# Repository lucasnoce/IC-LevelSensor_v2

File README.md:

# IC-LevelSensor_v2
This is version 2 of an IoT device designed to measure water levels using an ultrasonic sensing module and transmit the acquired data via NBIoT.

## Summary
Similar to version 1, the system employs an AJ-SR04M ultrasonic sensing module now connected to a STM32L476RGT6 microcontroller. This module measures the time interval it takes for an ultrasonic wave to travel from the transducer to the water level and back. By calculating the distance based on the time duration, the speed of sound, and dividing the result by 2, the accurate water level is determined. As the speed of sound varies based on factors such as temperature, humidity, and pressure, a SHT31-DIS sensor is incorporated to measure temperature and humidity (pressure is assumed constant). This additional information allows for precise estimation of the speed of sound just before each distance measurement is taken.

To transmit data to the TagoIO platform, a SIM7020 NBIoT module is utilized, employing the MQTT protocol. This facilitates the configuration of a comprehensive dashboard displaying variations in water and battery levels, local temperature and humidity over time, making it an excellent solution for monitoring purposes.

The device is specifically designed for deployment in remote environments and operates on battery power. Due to this constraint, the system primarily operates in low-power mode and wakes up periodically. In this initial version of the device, the wake-up period is intentionally kept small, and collected data is transmitted during each wake-up event via NBIoT. This design choice aims to facilitate easier debugging and testing of the device's functionality. Because it is designed to be battery powered, the device can monitor battery voltage through the microcontroller's ADC.

## Designed PCB
The following image shows the designed PCB layout. It incorporates the SMT32, SHT31, SIM7020E and its adjacent circuitry onto the layout, only leaving the AJ-SR04M as an external module. The PCB features a P-Channel MOSFET at power input for low power reverse polarity protection, a selectable current sensing shunt resistor and ESD protection on the USB connector, SIM Card socket and SIM7020 power input tantalum capacitors. Also features IPEX connector for external antenna with impedance matched trace. The board works on 3.3V and can be powered either by 1.5V batteries such as AAA (through TPS613221ADBV DC-DC boost converter) or by the Micro USB type B (through AMS1117-3.3 regulator).

## Software
Still under development, all drivers and functionalities will be implemented from scratch through STM32CubeIDE.

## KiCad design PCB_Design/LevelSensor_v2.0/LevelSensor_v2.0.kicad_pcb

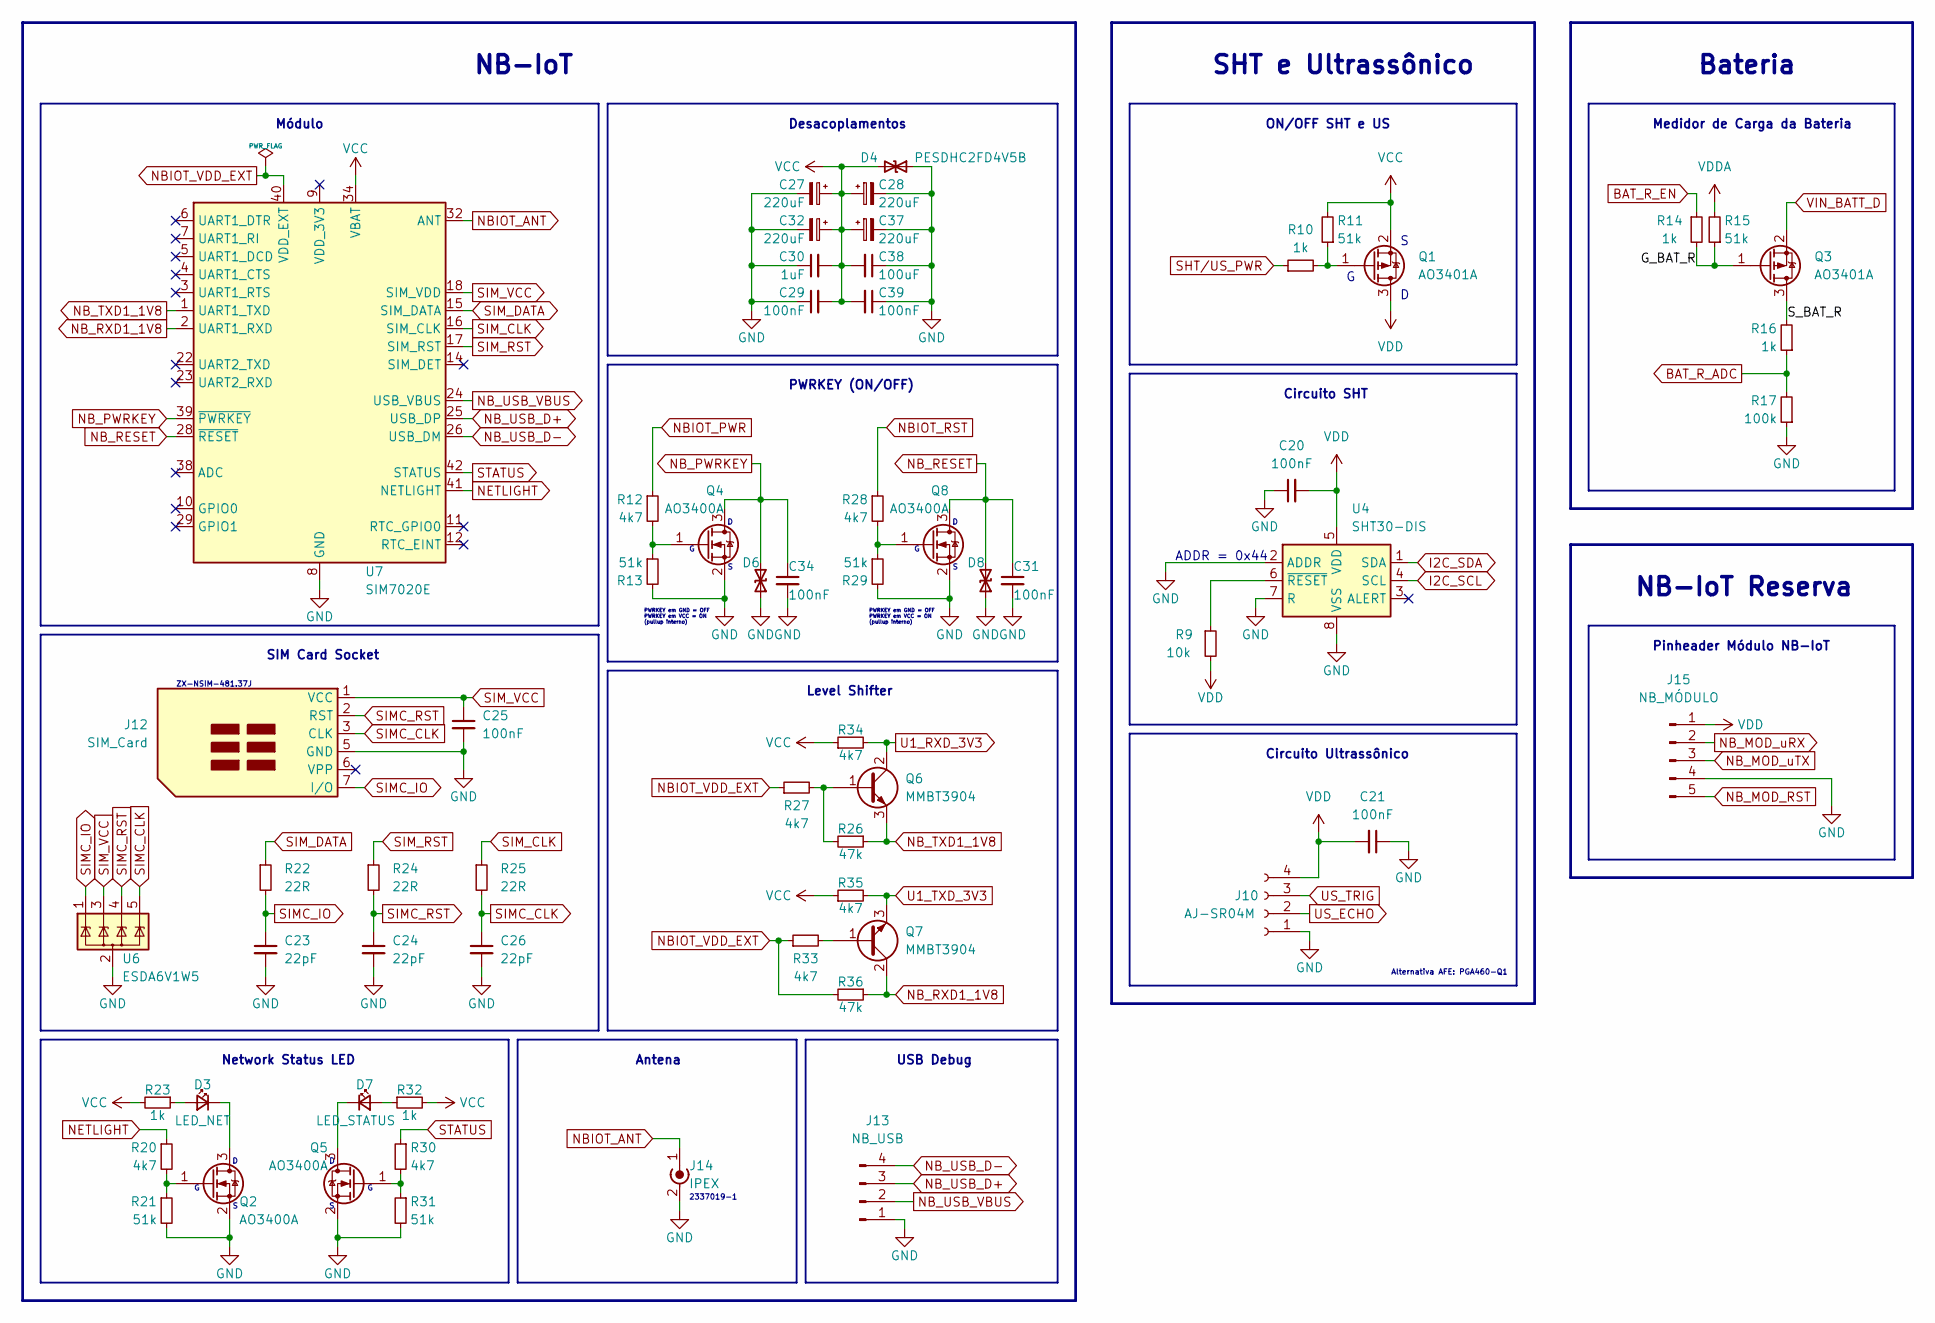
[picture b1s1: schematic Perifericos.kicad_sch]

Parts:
C20, C21: 100nF; C_0603_1608Metric; LCSC Part Number C14663
C23, C24, C26: 22pF; C_0402_1005Metric; LCSC Part Number C1555
C25, C29, C31, C34, C39: 100nF; C_0402_1005Metric; LCSC Part Number C1525
C27, C28, C32, C37: 220uF; CP_EIA-3528-12_Kemet-T
C30: 1uF; C_0402_1005Metric; LCSC Part Number C52923
C38: 100uF; C_1206_3216Metric; LCSC Part Number C15008
D3: LED_NET; LED_0603_1608Metric; LCSC Part Number C2286
D4, D6, D8: PESDHC2FD4V5B; D_TVS_DFN1006-2L
D7: LED_STATUS; LED_0603_1608Metric; LCSC Part Number C72041
J10: AJ-SR04M
J12: SIM_Card; NanoSIMCard-Socket_ZX-NSIM-281.4J
J13: NB_USB; PinHeader_1x04_P2.54mm_Vertical
J14: IPEX; Conn_RF_Receptacle_SMT-TE_2337019-1
J15: NB_MÓDULO; PinHeader_1x05_P2.54mm_Vertical
Q1, Q3: AO3401A; SOT-23; LCSC Part Number C15127
Q2, Q4, Q5, Q8: AO3400A; SOT-23; LCSC Part Number C20917
Q6, Q7: MMBT3904; TBJ_SOT-23; LCSC Part Number C20526
R9: 10k; R_0603_1608Metric; LCSC Part Number C25804
R10, R14, R16, R23, R32: 1k; R_0603_1608Metric; LCSC Part Number C21190
R11, R13, R15, R21, R29, R31: 51k; R_0603_1608Metric; LCSC Part Number C23196
R12, R20, R27, R28, R30, R33, R34, R35: 4k7; R_0603_1608Metric; LCSC Part Number C23162
R17: 100k; R_0603_1608Metric; LCSC Part Number C25803
R22, R24, R25: 22R; R_0402_1005Metric; LCSC Part Number C25092
R26, R36: 47k; R_0603_1608Metric; LCSC Part Number C25819
U4: SHT30-DIS; Sensirion_DFN-8-1EP_2.5x2.5mm_P0.5mm_EP1.1x1.7mm; LCSC Part Number C2687423
U6: ESDA6V1W5; SOT323-5L; LCSC Part Number C167129
U7: SIM7020E; SIMCom_SIM800C; LCSC Part Number C194746

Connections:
/Perifericos/G_BAT_R: Q3.1 (G), R14.2, R15.1
/Perifericos/S_BAT_R: Q3.3 (D), R16.2
BAT_R_ADC: R16.1, R17.2; also elsewhere on the board
BAT_R_EN: R14.1; also elsewhere on the board
GND: C20.1, C21.1, C23.2, C24.2, C25.2, C26.2, C27.2, C28.2, C29.1, C30.1, C31.2, C32.2, C34.2, C37.2, C38.1, C39.1, D4.1 (A1), D6.1 (A1), D8.1 (A1), J10.1, J12.5 (GND), J13.1, J14.2 (Ext), J15.4, Q2.2 (S), Q4.2 (S), Q5.2 (S), Q8.2 (S), R13.2, R17.1, R21.2, R29.2, R31.2, U4.2 (ADDR), U4.7 (R), U4.8 (VSS), U4.9 (VSS), U6.2 (GND), U7.8 (GND), U7.13 (GND), U7.19 (GND), U7.21 (GND), U7.27 (GND), U7.30 (GND), U7.31 (GND), U7.33 (GND), U7.36 (GND), U7.37 (GND); also elsewhere on the board
I2C_SCL: U4.4 (SCL); also elsewhere on the board
I2C_SDA: U4.1 (SDA); also elsewhere on the board
NBIOT_ANT: J14.1 (In), U7.32 (ANT)
NBIOT_PWR: R12.1; also elsewhere on the board
NBIOT_RST: R28.1; also elsewhere on the board
NBIOT_VDD_EXT: R27.1, R33.1, R36.2, U7.40 (VDD_EXT)
NB_MOD_RST: J15.5; also elsewhere on the board
NB_MOD_uRX: J15.2; also elsewhere on the board
NB_MOD_uTX: J15.3; also elsewhere on the board
NB_PWRKEY: C34.1, D6.2 (A2), Q4.3 (D), U7.39 (~PWRKEY)
NB_RESET: C31.1, D8.2 (A2), Q8.3 (D), U7.28 (~RESET)
NB_RXD1_1V8: Q7.2 (C), R36.1, U7.2 (UART1_RXD)
NB_TXD1_1V8: Q6.3 (E), R26.1, U7.1 (UART1_TXD)
NB_USB_D+: J13.3, U7.25 (USB_DP)
NB_USB_D-: J13.4, U7.26 (USB_DM)
NB_USB_VBUS: J13.2, U7.24 (USB_VBUS)
NETLIGHT: R20.1, U7.41 (NETLIGHT)
unnamed: D3.1 (K), Q2.3 (D)
unnamed: D3.2 (A), R23.1
unnamed: D7.1 (K), Q5.3 (D)
unnamed: D7.2 (A), R32.1
unnamed: Q1.1 (G), R10.2, R11.1
unnamed: Q2.1 (G), R20.2, R21.1
unnamed: Q4.1 (G), R12.2, R13.1
unnamed: Q5.1 (G), R30.2, R31.1
unnamed: Q6.1 (B), R26.2, R27.2
unnamed: Q7.1 (B), R33.2
unnamed: Q8.1 (G), R28.2, R29.1
unnamed: R9.1, U4.6 (~RESET)
SHT/US_PWR: R10.1; also elsewhere on the board
SIMC_CLK: C26.1, J12.3 (CLK), R25.2, U6.5 (IO5)
SIMC_IO: C23.1, J12.7 (I/O), R22.2, U6.1 (IO1)
SIMC_RST: C24.1, J12.2 (RST), R24.2, U6.4 (IO4)
SIM_CLK: R25.1, U7.16 (SIM_CLK)
SIM_DATA: R22.1, U7.15 (SIM_DATA)
SIM_RST: R24.1, U7.17 (SIM_RST)
SIM_VCC: C25.1, J12.1 (VCC), U6.3 (IO2), U7.18 (SIM_VDD)
STATUS: R30.1, U7.42 (STATUS)
U1_RXD_3V3: Q6.2 (C), R34.2; also elsewhere on the board
U1_TXD_3V3: Q7.3 (E), R35.2; also elsewhere on the board
US_ECHO: J10.2; also elsewhere on the board
US_TRIG: J10.3; also elsewhere on the board
VCC: C27.1, C28.1, C29.2, C30.2, C32.1, C37.1, C38.2, C39.2, D4.2 (A2), Q1.2 (S), R11.2, R23.2, R32.2, R34.1, R35.1, U7.34 (VBAT), U7.35 (VBAT); also elsewhere on the board
VDD: C20.2, C21.2, J10.4, J15.1, Q1.3 (D), R9.2, U4.5 (VDD)
VDDA: R15.2; also elsewhere on the board
VIN_BATT_D: Q3.2 (S); also elsewhere on the board

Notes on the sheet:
Circuito Ultrassônico
PWRKEY (ON/OFF)
Circuito SHT
PWRKEY em GND = OFF PWRKEY em VCC = ON (pullup interno)
Pinheader Módulo NB-IoT
ON/OFF SHT e US
2337019-1
Network Status LED
USB Debug
NB-IoT Reserva
Antena
NB-IoT
Bateria
Level Shifter
SIM Card Socket
Medidor de Carga da Bateria
SHT e Ultrassônico
Desacoplamentos
ZX-NSIM-481.37J
Alternativa AFE: PGA460-Q1
ADDR = 0x44
Módulo

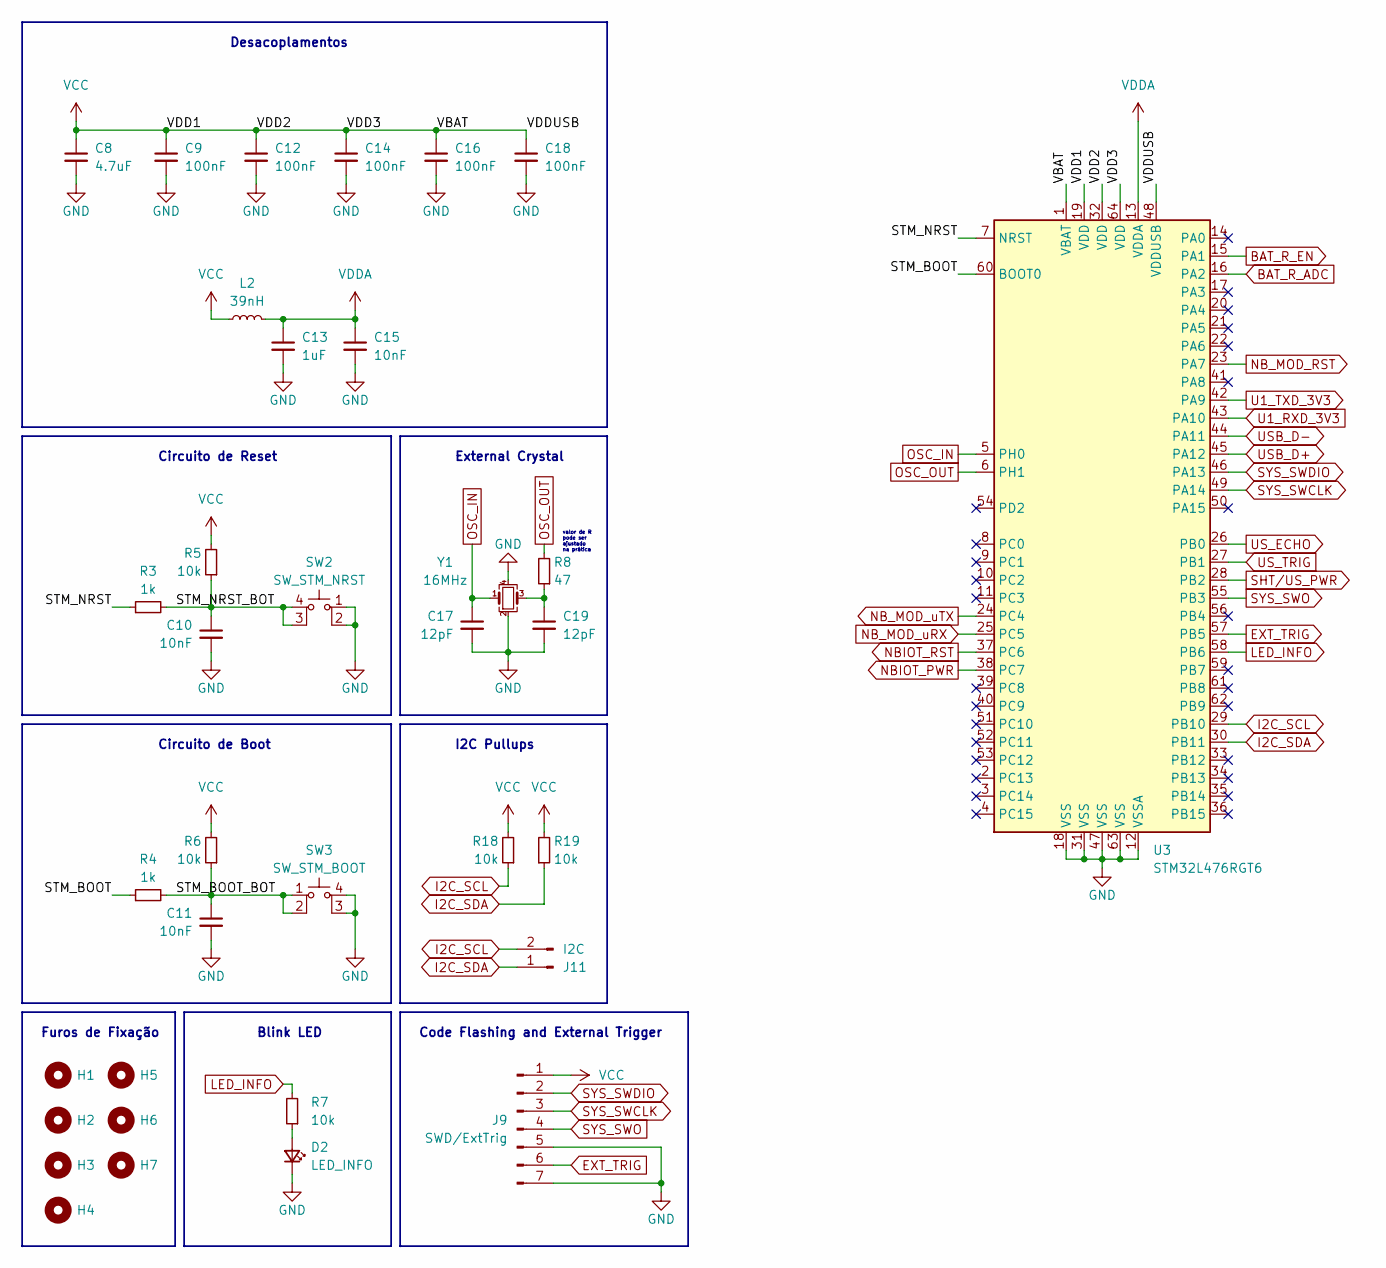
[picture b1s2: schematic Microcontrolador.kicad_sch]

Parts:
C8: 4.7uF; C_0603_1608Metric; LCSC Part Number C19666
C9, C12, C14, C16, C18: 100nF; C_0402_1005Metric; LCSC Part Number C1525
C10, C11: 10nF; C_0603_1608Metric; LCSC Part Number C57112
C13: 1uF; C_0402_1005Metric; LCSC Part Number C52923
C15: 10nF; C_0402_1005Metric; LCSC Part Number C15195
C17, C19: 12pF; C_0402_1005Metric; LCSC Part Number C1547
D2: LED_INFO; LED_0603_1608Metric; LCSC Part Number C72041
H1, H2, H3, H4: SupPCB; MountingHole_2.2mm_M2
H5, H6, H7: ToolingHole; JLCPCB_ToolingHole
J9: SWD/ExtTrig; PinHeader_1x07_P2.54mm_Vertical
J11: I2C; PinHeader_1x02_P2.54mm_Vertical
L2: 39nH; L_0603_1608Metric
R3, R4: 1k; R_0603_1608Metric; LCSC Part Number C21190
R5, R6, R7, R18, R19: 10k; R_0603_1608Metric; LCSC Part Number C25804
R8: 47; R_0402_1005Metric; LCSC Part Number C25118
SW2: SW_STM_NRST; SW_TS-1187A-B-A-B; LCSC Part Number C318884
SW3: SW_STM_BOOT; SW_TS-1187A-B-A-B; LCSC Part Number C318884
U3: STM32L476RGT6; LQFP-64_10x10mm_P0.5mm; LCSC Part Number C74797
Y1: 16MHz; Crystal_SMD_Abracon_ABM8G-4Pin_3.2x2.5mm; LCSC Part Number C13738

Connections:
/Microcontrolador/STM_BOOT: R4.1, U3.60 (BOOT0)
/Microcontrolador/STM_BOOT_BOT: C11.1, R4.2, R6.1, SW3.1, SW3.2
/Microcontrolador/STM_NRST: R3.1, U3.7 (NRST)
/Microcontrolador/STM_NRST_BOT: C10.1, R3.2, R5.1, SW2.3 (K), SW2.4 (A)
BAT_R_ADC: U3.16 (PA2); also elsewhere on the board
BAT_R_EN: U3.15 (PA1); also elsewhere on the board
EXT_TRIG: J9.6, U3.57 (PB5)
GND: C8.2, C9.2, C10.2, C11.2, C12.2, C13.2, C14.2, C15.2, C16.2, C17.2, C18.2, C19.2, D2.1 (K), J9.5, J9.7, SW2.1, SW2.2, SW3.3 (K), SW3.4 (A), U3.12 (VSSA), U3.18 (VSS), U3.31 (VSS), U3.47 (VSS), U3.63 (VSS), Y1.2, Y1.4; also elsewhere on the board
I2C_SCL: J11.2, R18.1, U3.29 (PB10); also elsewhere on the board
I2C_SDA: J11.1, R19.1, U3.30 (PB11); also elsewhere on the board
LED_INFO: R7.2, U3.58 (PB6)
NBIOT_PWR: U3.38 (PC7); also elsewhere on the board
NBIOT_RST: U3.37 (PC6); also elsewhere on the board
NB_MOD_RST: U3.23 (PA7); also elsewhere on the board
NB_MOD_uRX: U3.25 (PC5); also elsewhere on the board
NB_MOD_uTX: U3.24 (PC4); also elsewhere on the board
unnamed: C19.1, R8.1, Y1.3
unnamed: D2.2 (A), R7.1
OSC_IN: C17.1, U3.5 (PH0), Y1.1
OSC_OUT: R8.2, U3.6 (PH1)
SHT/US_PWR: U3.28 (PB2); also elsewhere on the board
SYS_SWCLK: J9.3, U3.49 (PA14)
SYS_SWDIO: J9.2, U3.46 (PA13)
SYS_SWO: J9.4, U3.55 (PB3)
U1_RXD_3V3: U3.43 (PA10); also elsewhere on the board
U1_TXD_3V3: U3.42 (PA9); also elsewhere on the board
USB_D+: U3.45 (PA12); also elsewhere on the board
USB_D-: U3.44 (PA11); also elsewhere on the board
US_ECHO: U3.26 (PB0); also elsewhere on the board
US_TRIG: U3.27 (PB1); also elsewhere on the board
VCC: C8.1, C9.1, C12.1, C14.1, C16.1, C18.1, J9.1, L2.1, R5.2, R6.2, R18.2, R19.2, U3.1 (VBAT), U3.19 (VDD), U3.32 (VDD), U3.48 (VDDUSB), U3.64 (VDD); also elsewhere on the board
VDDA: C13.1, C15.1, L2.2, U3.13 (VDDA); also elsewhere on the board

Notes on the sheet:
I2C Pullups
External Crystal
Desacoplamentos
Circuito de Boot
Blink LED
valor de R pode ser ajustado na prática
Furos de Fixação
Circuito de Reset
Code Flashing and External Trigger

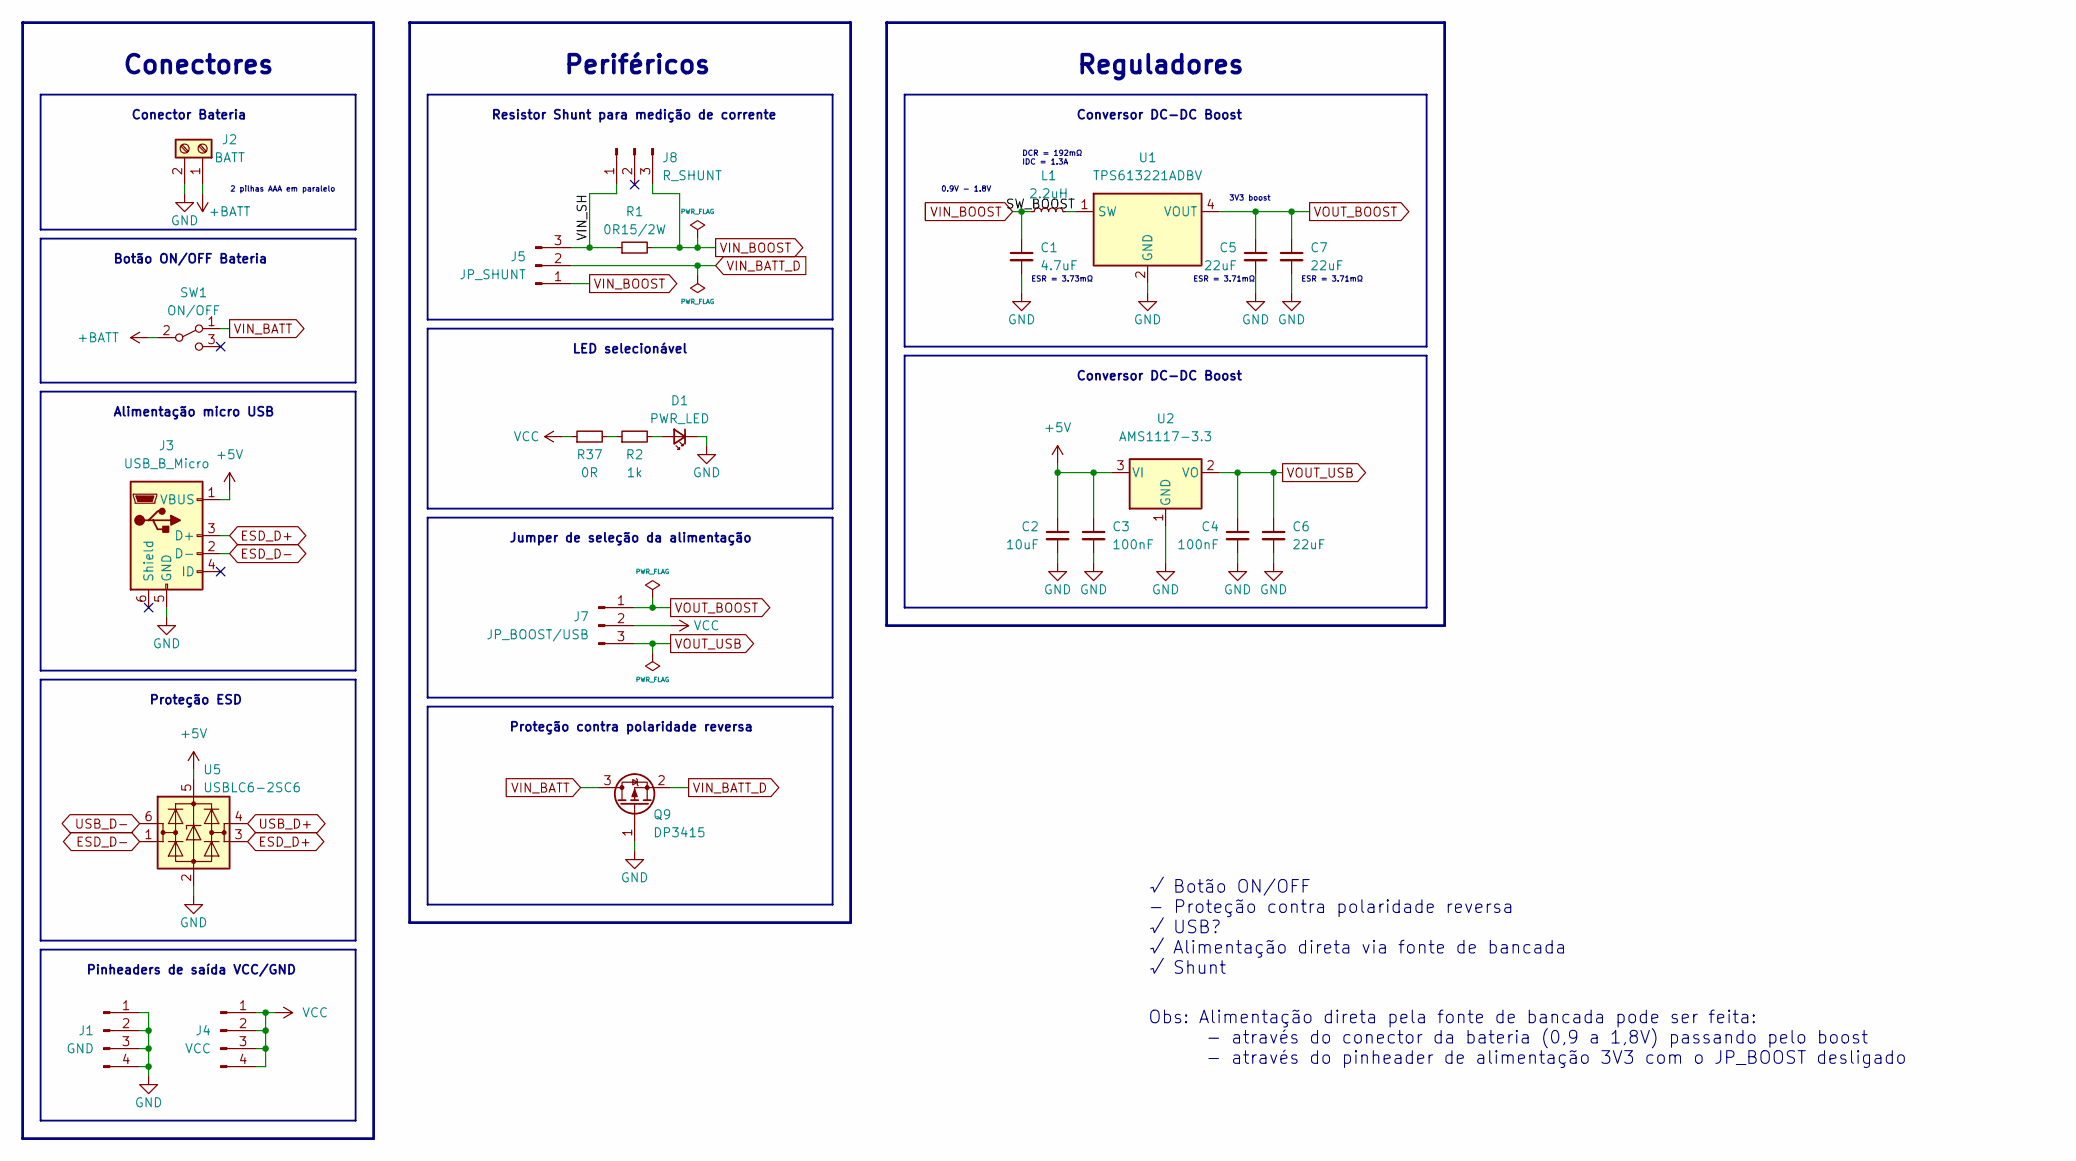
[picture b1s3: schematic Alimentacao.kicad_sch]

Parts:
C1: 4.7uF; C_0603_1608Metric; LCSC Part Number C19666
C2: 10uF; C_0603_1608Metric; LCSC Part Number C19702
C3, C4: 100nF; C_0402_1005Metric; LCSC Part Number C1525
C5, C6, C7: 22uF; C_0603_1608Metric; LCSC Part Number C59461
D1: PWR_LED; LED_0603_1608Metric; LCSC Part Number C2286
J1: GND; PinHeader_1x04_P2.54mm_Vertical
J2: BATT; ScrewTerminal_1x2P_P5mm
J3: USB_B_Micro; USB_Micro_B-Dealon_USB-MR-D-015
J4: VCC; PinHeader_1x04_P2.54mm_Vertical
J5: JP_SHUNT; PinHeader_1x03_P2.54mm_Vertical_SMD_Pin1Left
J7: JP_BOOST/USB; PinHeader_1x03_P2.54mm_Vertical
J8: R_SHUNT; PinHeader_1x03_P2.54mm_Vertical_SMD_Pin1Left
L1: 2.2uH; L_SMD-FNR4030S2R2MT
Q9: DP3415; PMOS_DP3415_SOT-23; LCSC Part Number C15127
R1: 0R15/2W; R_2512_6332Metric
R2: 1k; R_0603_1608Metric; LCSC Part Number C21190
R37: 0R; SolderJumper-2_P1.3mm_Open_RoundedPad1.0x1.5mm
SW1: ON/OFF; SW_SPDT_SS-12D10-G090
U1: TPS613221ADBV; SOT-23-5; LCSC Part Number C2070813
U2: AMS1117-3.3; SOT-223-3_TabPin2; LCSC Part Number C6186
U5: USBLC6-2SC6; SOT-23-6

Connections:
+5V: C2.1, C3.1, J3.1 (VBUS), U2.3 (VI), U5.5 (VBUS)
+BATT: J2.1, SW1.2 (B)
/Alimentacao/SW_BOOST: L1.2, U1.1 (SW)
/Alimentacao/VIN_SH: J5.3, J8.1, R1.1
ESD_D+: J3.3 (D+), U5.3 (I/O2)
ESD_D-: J3.2 (D-), U5.1 (I/O1)
GND: C1.2, C2.2, C3.2, C4.2, C5.2, C6.2, C7.2, D1.1 (K), J1.1, J1.2, J1.3, J1.4, J2.2, J3.5 (GND), Q9.1 (G), U1.2 (GND), U2.1 (GND), U5.2 (GND); also elsewhere on the board
unnamed: D1.2 (A), R2.2
unnamed: R2.1, R37.2
USB_D+: U5.4 (I/O2); also elsewhere on the board
USB_D-: U5.6 (I/O1); also elsewhere on the board
VCC: J4.1, J4.2, J4.3, J4.4, J7.2, R37.1; also elsewhere on the board
VIN_BATT: Q9.3 (D), SW1.1 (A)
VIN_BATT_D: J5.2, Q9.2 (S); also elsewhere on the board
VIN_BOOST: C1.1, J5.1, J8.3, L1.1, R1.2
VOUT_BOOST: C5.1, C7.1, J7.1, U1.4 (VOUT)
VOUT_USB: C4.1, C6.1, J7.3, U2.2 (VO)

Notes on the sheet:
Conectores
Obs: Alimentação direta pela fonte de bancada pode ser feita: - através do conector da bateria (0,9 a 1,8V) passando pelo boost - através do pinheader de alimentação 3V3 com o JP_BOOST desligado
Resistor Shunt para medição de corrente
Jumper de seleção da alimentação
ESR = 3.73mΩ
ESR = 3.71mΩ
Reguladores
Conversor DC-DC Boost
DCR = 192mΩ IDC = 1.3A
3V3 boost
Alimentação micro USB
√ Botão ON/OFF - Proteção contra polaridade reversa √ USB? √ Alimentação direta via fonte de bancada √ Shunt
Botão ON/OFF Bateria
Conector Bateria
0.9V - 1.8V
Proteção ESD
LED selecionável
Pinheaders de saída VCC/GND
2 pilhas AAA em paralelo
Periféricos
Proteção contra polaridade reversa

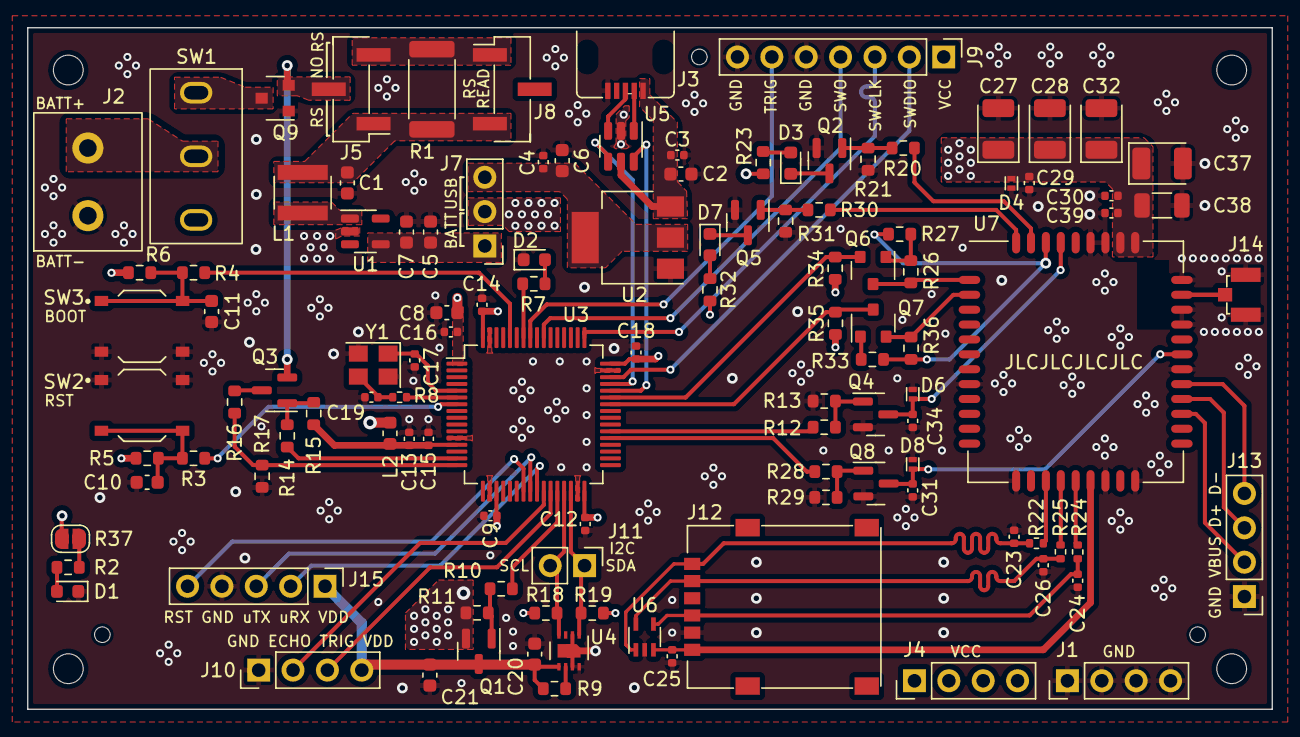
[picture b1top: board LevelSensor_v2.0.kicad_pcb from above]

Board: 4 copper layers, 92.0 x 50.4 mm, 122 parts (0 on the bottom side), 78 nets.

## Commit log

2023-11-26 Create PCB_Design folder
2023-11-26 Create 3D_Models folder
2023-12-01 Create 3D_Case folder
